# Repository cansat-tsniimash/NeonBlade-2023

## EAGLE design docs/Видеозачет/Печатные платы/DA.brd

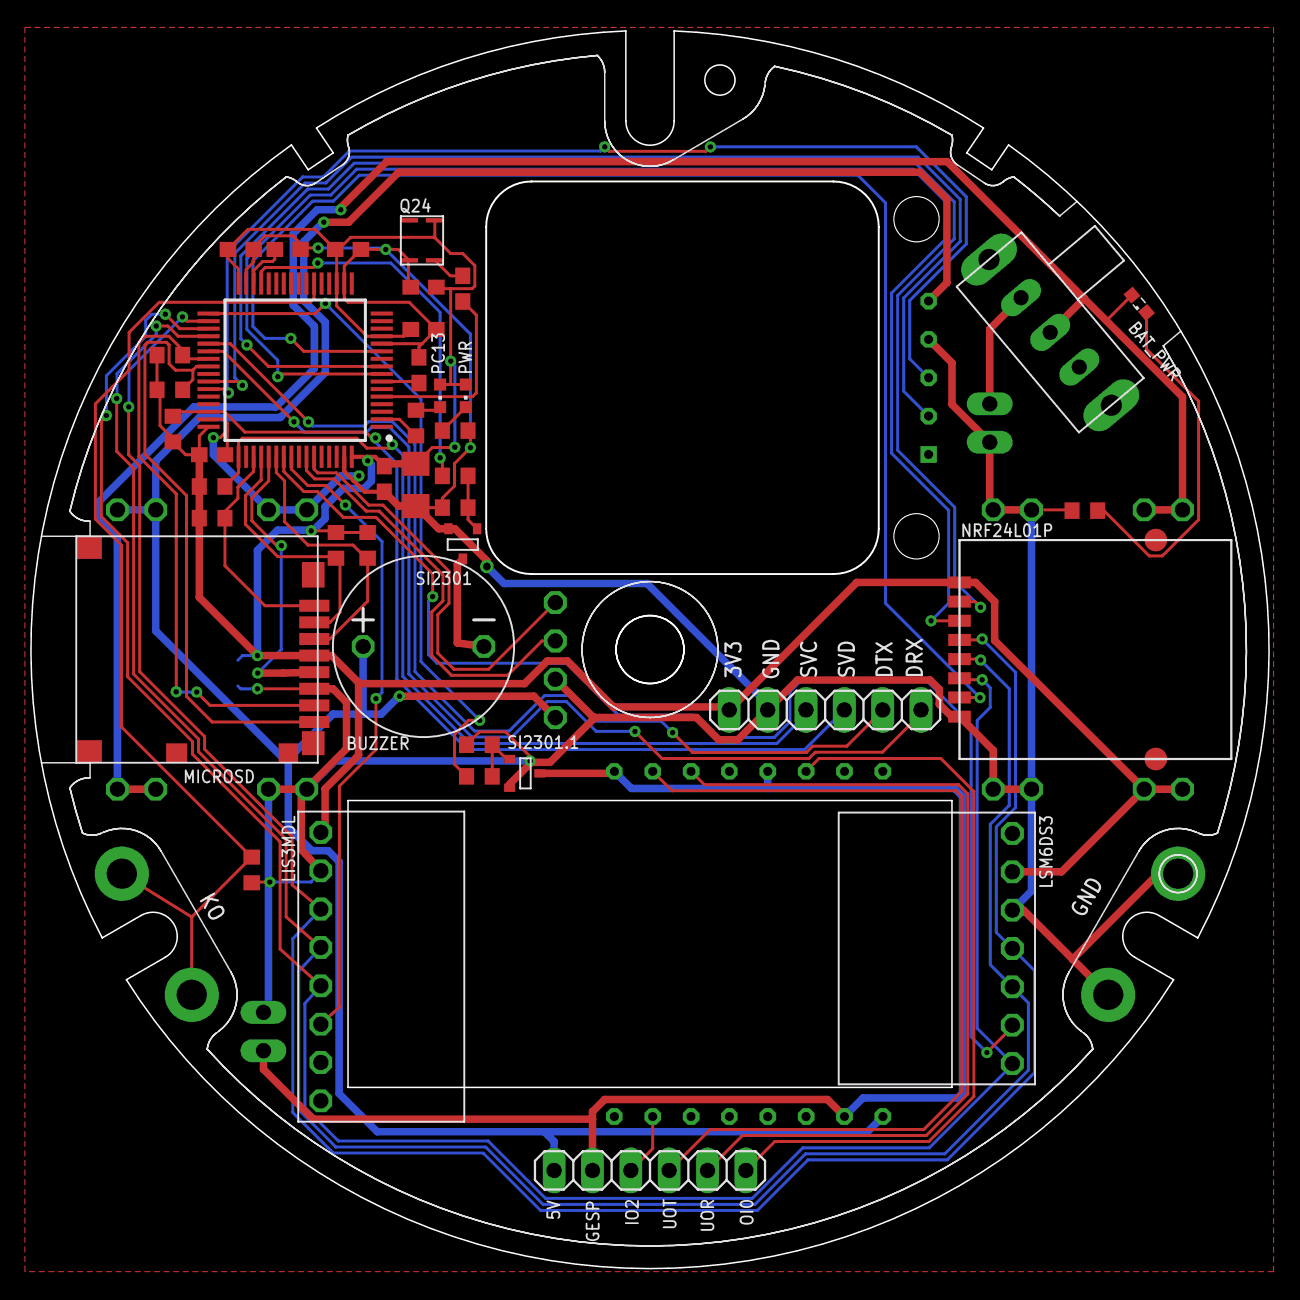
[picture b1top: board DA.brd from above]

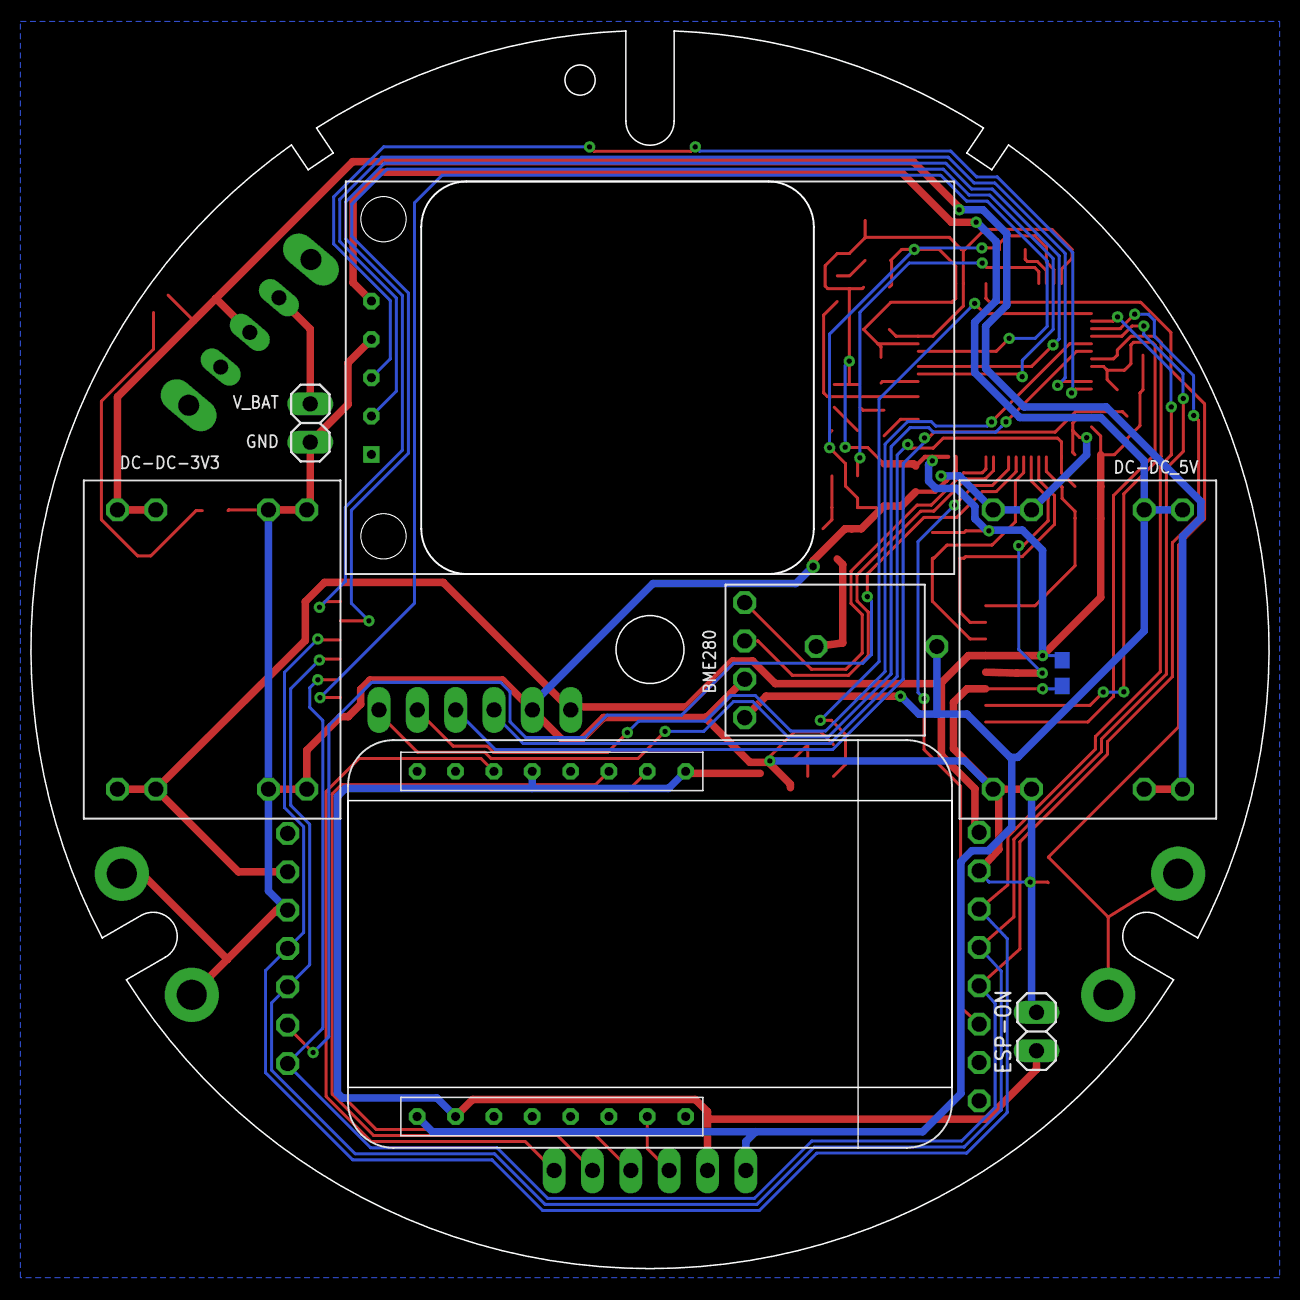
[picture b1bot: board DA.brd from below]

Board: 2 copper layers, 82.0 x 82.0 mm, 48 parts (7 on the bottom side), 46 nets.

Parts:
BAT_PWR: SML0603
BME280: BME280BME280-PINS-ONLY; BME280-PINS-ONLY
BUZZER: BUZZERS8R6; BUZZER-S8R12
C1, C3, C4, C5, C6, C7: 100nF; C0603
C2: 10uF; C1206
C8: 1nF; C0603
C9: 100nf; C0603
C10: 10nF; C0603
C11: 4.7uf; C0603
DC-DC-3V3: MP1584-B
DC-DC_5V: MP1584-B
ESP32-CAM: ESP32-CAM
ESP-ON: 1X02
JP1, JP3: 1X06
JP2: 1X02
LIS3MDL: LIS3MDL-CJMCUбез_отв.; LIS3MDL-CGMSU-NB2023-1
LSM6DS3: LSM6DS3-GY-NB2023Без_отв.; LSM6DS3-GY-NB2023-1
MICROSD: SD
NRF24L01P: NRF24L01_ML01SP4
PC13: CHIPLED_0603
PWR: CHIPLED_0603
Q24: Q24
R1: 5K1; R0603
R2, R7, R8, R9, R10: 3k3; R0603
R3, R4: 2k; R0603
R5, R6, R31, R32, R33: 10k; R0603
R30, R34: 100R; R0603
S1: SWITCH_SK-12F14
SI2301, SI2301.1: MOSFET-N; SOT23-3
STM32F0401: STM32F401RCT6; QFP50P1200X1200X160-64N
U$5: GPS_NEO7M_W-PPS; GPS_NEO7M_W-PPS_&_ANT

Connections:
3V3: C1.2, C2.1, C3.2, C4.1, C5.1, C6.1, C7.2, C10.2, DC-DC-3V3.P$7, DC-DC-3V3.P$8, JP1.6, LIS3MDL.P$1, LSM6DS3.P$6, MICROSD.VDD, NRF24L01P.P$1, PC13.A, PWR.A, Q24.P$4, R2.2, R5.2, R6.2, R7.2, R8.2, R9.2, R10.2, STM32F0401.13, STM32F0401.19, STM32F0401.32, STM32F0401.48, STM32F0401.64
5V: BME280.P$1, BUZZER.P$1, DC-DC_5V.P$7, DC-DC_5V.P$8, ESP32-CAM.P$1, JP3.1, U$5.VCC
BASS_BUZZER: R30.1, STM32F0401.29
CE_NRF: NRF24L01P.P$2, STM32F0401.9
CS_LIS: LIS3MDL.P$6, STM32F0401.56
CS_LSM: LSM6DS3.P$2, STM32F0401.55
CS_NRF: NRF24L01P.P$3, STM32F0401.8
DBG_RX: JP1.1, STM32F0401.38
DBG_TX: JP1.2, STM32F0401.37
ESP_EN: R34.1, STM32F0401.33
GND: BME280.P$2, C1.1, C2.2, C3.1, C4.2, C5.2, C6.2, C7.1, C9.1, C10.1, C11.2, DC-DC-3V3.P$3, DC-DC-3V3.P$4, DC-DC-3V3.P$5, DC-DC-3V3.P$6, DC-DC_5V.P$3, DC-DC_5V.P$4, DC-DC_5V.P$5, DC-DC_5V.P$6, ESP-ON.1, JP1.5, JP2.2, LIS3MDL.P$2, LSM6DS3.P$5, MICROSD.VSS, NRF24L01P.P$8, Q24.P$2, R1.2, R3.1, R31.2, R32.1, R33.1, SI2301.2, SI2301.1.2, STM32F0401.12, STM32F0401.18, STM32F0401.31, STM32F0401.47, STM32F0401.63, U$5.GND
GND_ESP: ESP32-CAM.P$2, ESP32-CAM.P$12, ESP32-CAM.P$16, ESP-ON.2, JP3.2, SI2301.1.3
GPS_RX: STM32F0401.43, U$5.TX
GPS_TX: STM32F0401.42, U$5.RX
IO0: ESP32-CAM.P$11, JP3.6
IO2: ESP32-CAM.P$7, JP3.3
KO: R32.2, STM32F0401.22
LED: R4.1, STM32F0401.2
MISO: LIS3MDL.P$5, LSM6DS3.P$1, NRF24L01P.P$6, STM32F0401.35
MOSI: LIS3MDL.P$4, LSM6DS3.P$3, NRF24L01P.P$5, STM32F0401.36
unnamed: R30.2, R31.1, SI2301.1
unnamed: R33.2, R34.2, SI2301.1.1
unnamed: BAT_PWR.C, R1.1
unnamed: JP2.1, S1.P$5
unnamed: C8.2, Q24.P$3
unnamed: C11.1, STM32F0401.30
unnamed: BUZZER.P$2, SI2301.3
unnamed: PWR.C, R3.2
unnamed: PC13.C, R4.2
NRF_IRQ: NRF24L01P.P$7, STM32F0401.11
NRST: C9.2, STM32F0401.7
SCK: LIS3MDL.P$3, LSM6DS3.P$4, NRF24L01P.P$4, STM32F0401.34
SCL: BME280.P$3, STM32F0401.58
SDA: BME280.P$4, STM32F0401.59
SDIO_CK: MICROSD.CLK, STM32F0401.53
SDIO_CMD: MICROSD.CMD, R8.1, STM32F0401.54
SDIO_DAT0: MICROSD.DAT0, R9.1, STM32F0401.39
SDIO_DAT1: MICROSD.DAT1, R10.1, STM32F0401.40
SDIO_DAT2: MICROSD.DAT2, R2.1, STM32F0401.51
SDIO_DAT3: MICROSD.DAT3, R7.1, STM32F0401.52
SVC: JP1.4, R6.1, STM32F0401.49
SVD: JP1.3, R5.1, STM32F0401.46
TCXO: C8.1, STM32F0401.5
UOR: ESP32-CAM.P$14, JP3.5
UOT: ESP32-CAM.P$15, JP3.4
V_BAT: BAT_PWR.A, DC-DC-3V3.P$1, DC-DC-3V3.P$2, DC-DC_5V.P$1, DC-DC_5V.P$2, S1.P$3

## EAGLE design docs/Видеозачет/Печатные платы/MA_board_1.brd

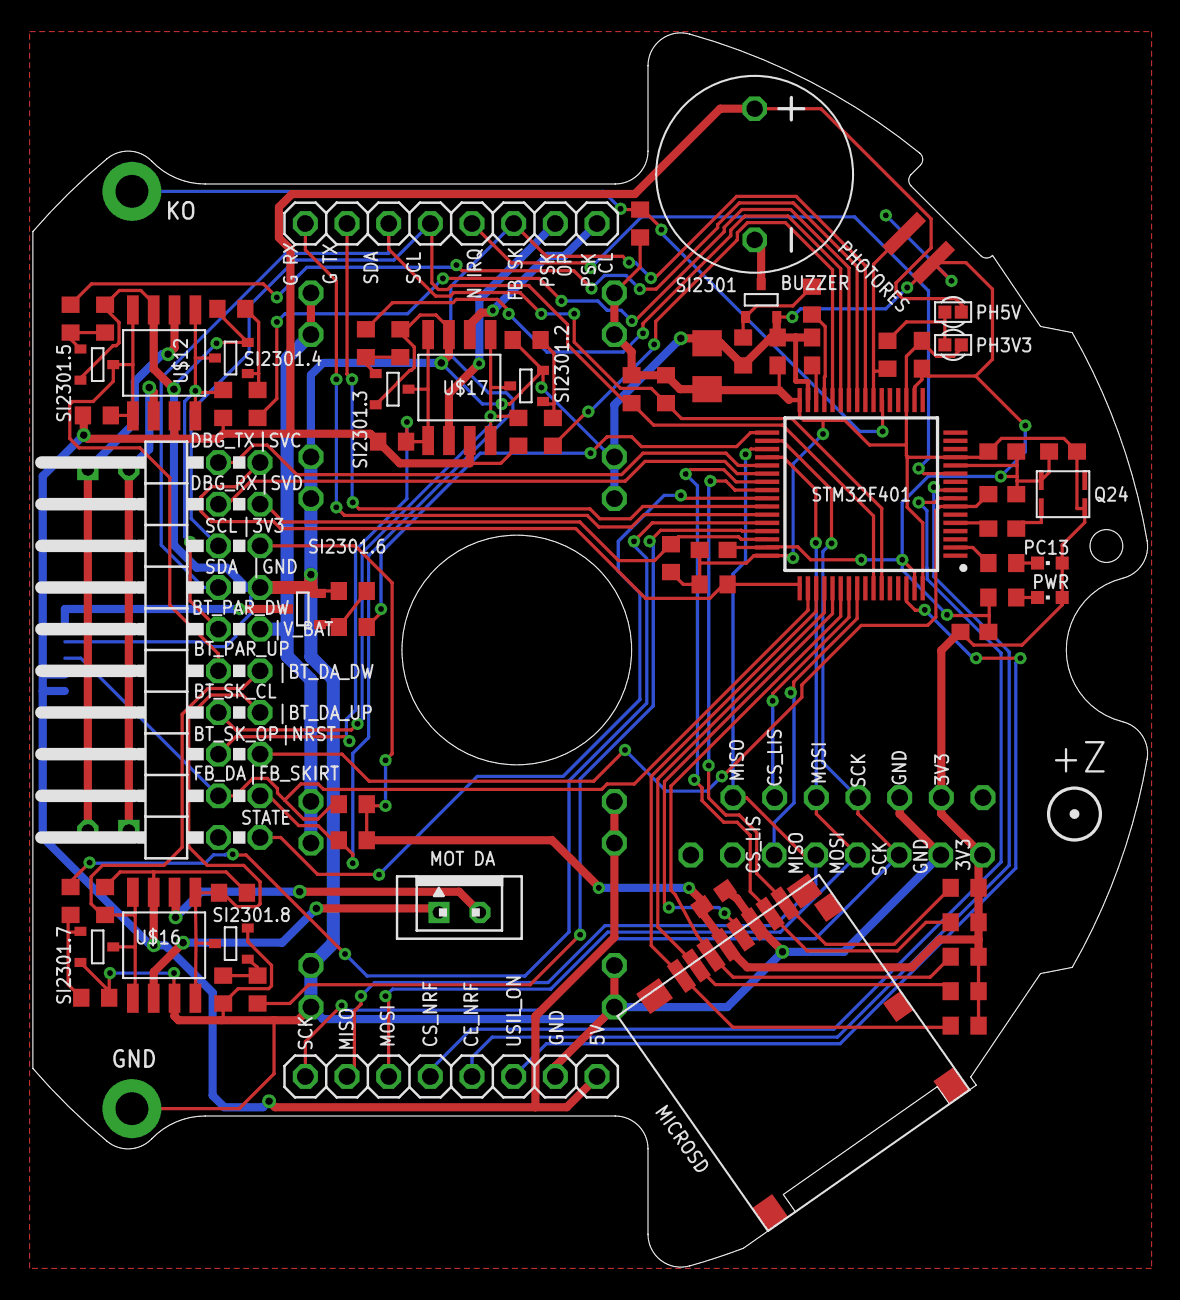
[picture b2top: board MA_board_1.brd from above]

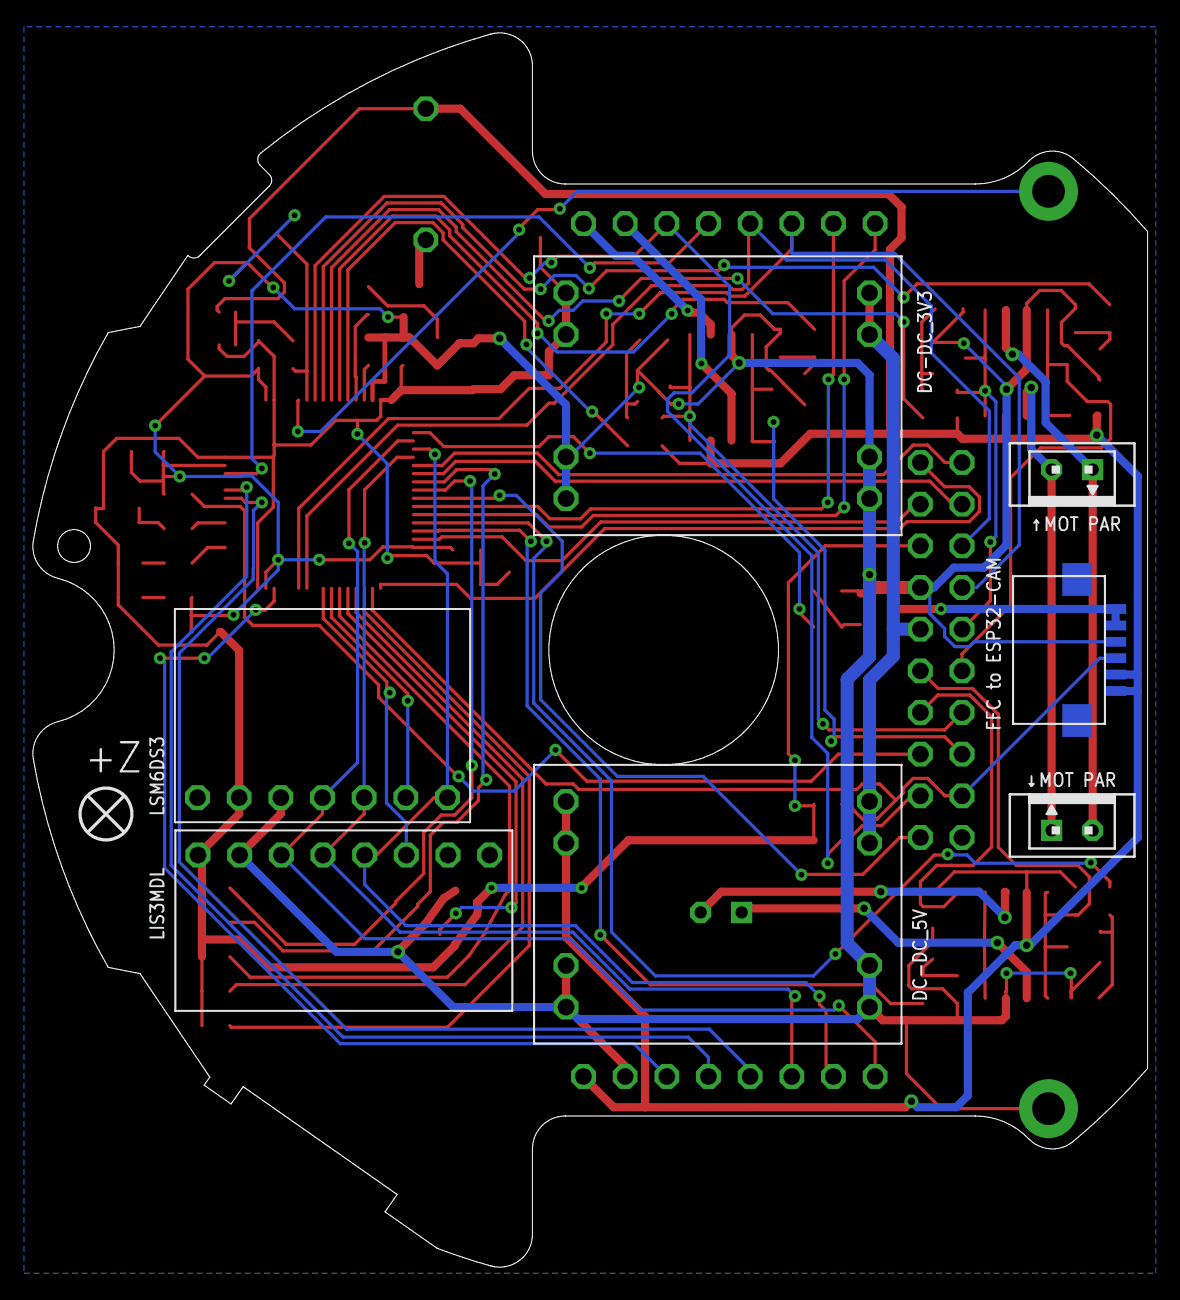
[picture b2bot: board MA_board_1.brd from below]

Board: 2 copper layers, 68.0 x 75.2 mm, 79 parts (5 on the bottom side), 70 nets.

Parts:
3V3, 5V: VIAS-CONNECT
BUZZER: BUZZERS8R6; BUZZER-S8R12
C1, C3, C4, C5, C6, C7, C9: 100nF; C0603
C2: 10uF; C1206
C8: 1nF; C0603
C10: 10nF; C0603
C11: 4.7uf; C0603
DC-DC_3V3, DC-DC_5V: MP1584-B
JP1: 2X10/90
JP2, JP3, JP4: JST-2-K-S; B2B-PH-K-S
JP6, JP7: 1X08
LIS3MDL: LIS3MDL-CJMCUБез_отв._зеркальный; LIS3MDL-CGMSU-NB2023
LSM6DS3: LSM6DS3-GY-NB2023
MICROSD: SD
PC13: CHIPLED_0603
PHOTORES: PHOTORES_VT93N1; PHOTORES_VT93N1_SMD
PWR: CHIPLED_0603
Q24: Q24
R1, R5, R6, R11, R12, R13, R14, R18, R19, R20, R21, R24, R25, R26, R27, R31, R33, R35: 10k; R0603
R2, R7, R8, R9, R10: 3k3; R0603
R3, R4: 2k; R0603
R15, R16, R22, R23, R28, R29, R30, R34: 100R; R0603
R17: 191k/2k; R0603
R32: 3k9; R0603
R36, R37: 4k7; R0603
SI2301, SI2301.2, SI2301.3, SI2301.4, SI2301.5, SI2301.6, SI2301.7, SI2301.8: MOSFET-N; SOT23-3
STM32F401: STM32F401RCT6; QFP50P1200X1200X160-64N
U$8: FCC-CONNECT-6P; FFC-CONNECT-6P-SMD
U$12, U$16, U$17: MOSFET_2P+2N_AP9930GM; SO8

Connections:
3V3: 3V3.1, C1.2, C2.1, C3.2, C4.1, C5.1, C6.1, C7.2, C10.2, DC-DC_3V3.P$7, DC-DC_3V3.P$8, JP1.15, LIS3MDL.P$1, LSM6DS3.P$6, MICROSD.VDD, PC13.A, PWR.A, Q24.P$4, R1.2, R2.2, R5.2, R6.2, R7.2, R8.2, R9.2, R10.2, R32.1, R35.1, R36.2, R37.2, STM32F401.13, STM32F401.19, STM32F401.32, STM32F401.48, STM32F401.64
5V: 5V.2, BUZZER.P$1, DC-DC_5V.P$7, DC-DC_5V.P$8, JP6.8, R12.2, R13.2, R19.2, R20.2, R25.2, R26.2, U$8.P$5, U$8.P$6, U$12.7, U$16.7, U$17.7
BASS_BUZZER: R30.1, STM32F401.29
BOTTON_DA_DOWN: JP1.9, R13.1, SI2301.7.3, U$16.1, U$16.8
BOTTON_DA_UP: JP1.7, R12.1, SI2301.8.3, U$16.4, U$16.5
BOTTON_PAR_DOWN: JP1.12, R20.1, SI2301.4.3, U$12.1, U$12.8
BOTTON_PAR_UP: JP1.10, R19.1, SI2301.5.3, U$12.4, U$12.5
BOTTON_SKIRT_CLOSE: JP1.8, R26.1, SI2301.2.3, U$17.1, U$17.8
BOTTON_SKIRT_OPEN: JP1.6, R25.1, SI2301.3.3, U$17.4, U$17.5
CE_NRF: JP6.5, STM32F401.9
CS_LIS: LIS3MDL.P$6, STM32F401.56
CS_LSM: LSM6DS3.P$2, STM32F401.55
CS_NRF: JP6.4, STM32F401.8
DBG_RX: JP1.18, STM32F401.38
DBG_TX: JP1.20, STM32F401.37
ESP_EN: R34.1, STM32F401.33
FEEDBACK_DA: JP1.4, R35.2, STM32F401.50, U$8.P$4
FEEDBACK_SKIRT: JP1.3, JP7.6, R1.1, STM32F401.24
GND: C1.1, C2.2, C3.1, C4.2, C5.2, C6.2, C7.1, C9.1, C10.1, C11.2, DC-DC_3V3.P$3, DC-DC_3V3.P$4, DC-DC_3V3.P$5, DC-DC_3V3.P$6, DC-DC_5V.P$3, DC-DC_5V.P$4, DC-DC_5V.P$5, DC-DC_5V.P$6, JP1.13, JP6.7, LIS3MDL.P$2, LSM6DS3.P$5, MICROSD.VSS, PHOTORES.P$1, Q24.P$2, R3.1, R11.1, R14.1, R18.1, R21.1, R24.1, R27.1, R31.2, R33.1, SI2301.2, SI2301.2.2, SI2301.3.2, SI2301.4.2, SI2301.5.2, SI2301.6.2, SI2301.7.2, SI2301.8.2, STM32F401.12, STM32F401.18, STM32F401.31, STM32F401.47, STM32F401.63, U$8.P$3, U$12.3, U$16.3, U$17.3
GND_ESP: SI2301.6.3, U$8.P$1, U$8.P$2
GPS_RX: JP7.1, STM32F401.43
GPS_TX: JP7.2, STM32F401.42
KO: R32.2, STM32F401.22
LED: R4.1, STM32F401.2
MISO: JP6.2, LIS3MDL.P$5, LSM6DS3.P$1, STM32F401.35
MOSI: JP6.3, LIS3MDL.P$4, LSM6DS3.P$3, STM32F401.36
MOTOR_DA_DOWN: R15.1, STM32F401.44
MOTOR_DA_UP: R16.2, STM32F401.45
MOTOR_PAR_DOWN: R22.1, STM32F401.26
MOTOR_PAR_UP: R23.2, STM32F401.25
MOTOR_SKIRT_CLOSE: R28.1, STM32F401.28
MOTOR_SKIRT_OPEN: R29.2, STM32F401.27
unnamed: R30.2, R31.1, SI2301.1
unnamed: R11.2, R15.2, SI2301.7.1
unnamed: R18.2, R22.2, SI2301.4.1
unnamed: R33.2, R34.2, SI2301.6.1
unnamed: JP3.1, JP4.2, U$12.2
unnamed: JP2.1, U$16.2
unnamed: JP2.2, U$16.6
unnamed: R14.2, R16.1, SI2301.8.1
unnamed: JP3.2, JP4.1, U$12.6
unnamed: C8.2, Q24.P$3
unnamed: R21.2, R23.1, SI2301.5.1
unnamed: C11.1, STM32F401.30
unnamed: 3V3.2, 5V.1, R17.1
unnamed: R24.2, R28.2, SI2301.2.1
unnamed: R27.2, R29.1, SI2301.3.1
unnamed: BUZZER.P$2, SI2301.3
unnamed: PWR.C, R3.2
unnamed: PC13.C, R4.2
NRF_IRQ: JP7.5, STM32F401.11
NRST: C9.2, JP1.5, STM32F401.7
PHOTORES: PHOTORES.P$2, R17.2, STM32F401.23
POWER_SKIRT_CLOSE: JP7.8, U$17.2
POWER_SKIRT_OPEN: JP7.7, U$17.6
SCK: JP6.1, LIS3MDL.P$3, LSM6DS3.P$4, STM32F401.34
SCL: JP1.16, JP7.4, R37.1, STM32F401.58
SDA: JP1.14, JP7.3, R36.1, STM32F401.59
SDIO_CK: MICROSD.CLK, STM32F401.53
SDIO_CMD: MICROSD.CMD, R8.1, STM32F401.54
SDIO_DAT0: MICROSD.DAT0, R9.1, STM32F401.39
SDIO_DAT1: MICROSD.DAT1, R10.1, STM32F401.40
SDIO_DAT2: MICROSD.DAT2, R2.1, STM32F401.51
SDIO_DAT3: MICROSD.DAT3, R7.1, STM32F401.52
STATE: JP1.1, STM32F401.41
SVC: JP1.19, R6.1, STM32F401.49
SVD: JP1.17, R5.1, STM32F401.46
TCXO: C8.1, STM32F401.5
USIL_ON: JP6.6, STM32F401.62
V_BAT: DC-DC_3V3.P$1, DC-DC_3V3.P$2, DC-DC_5V.P$1, DC-DC_5V.P$2, JP1.11

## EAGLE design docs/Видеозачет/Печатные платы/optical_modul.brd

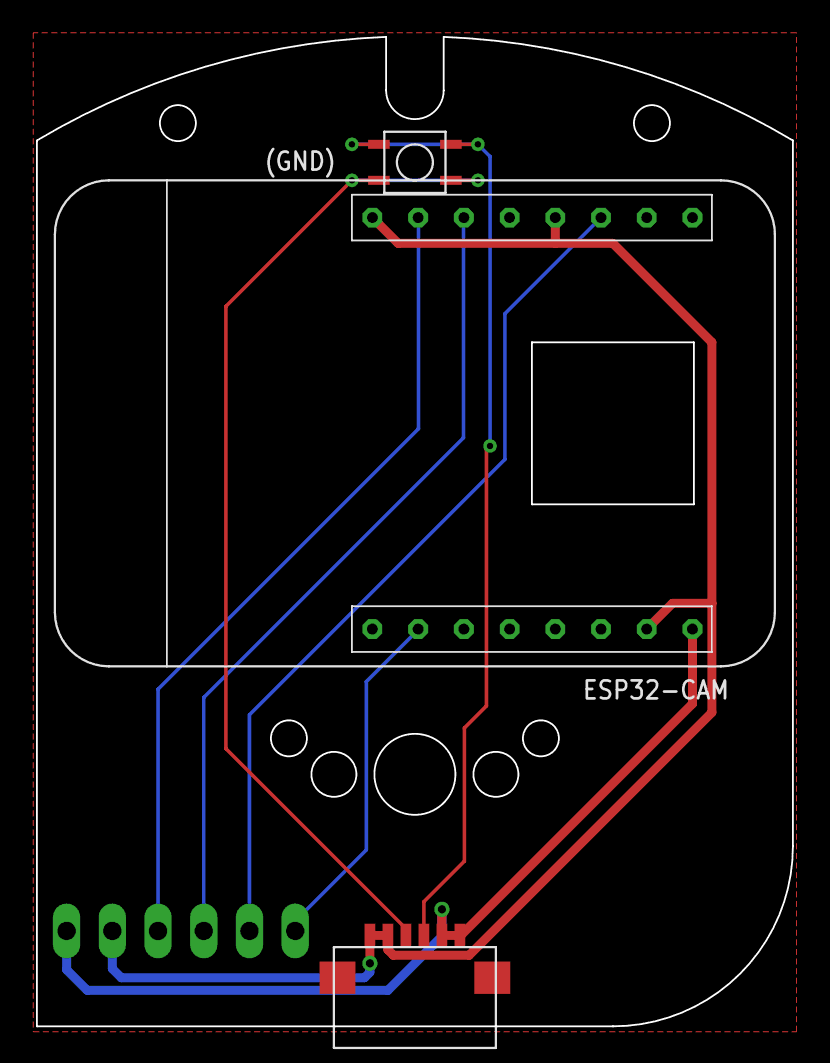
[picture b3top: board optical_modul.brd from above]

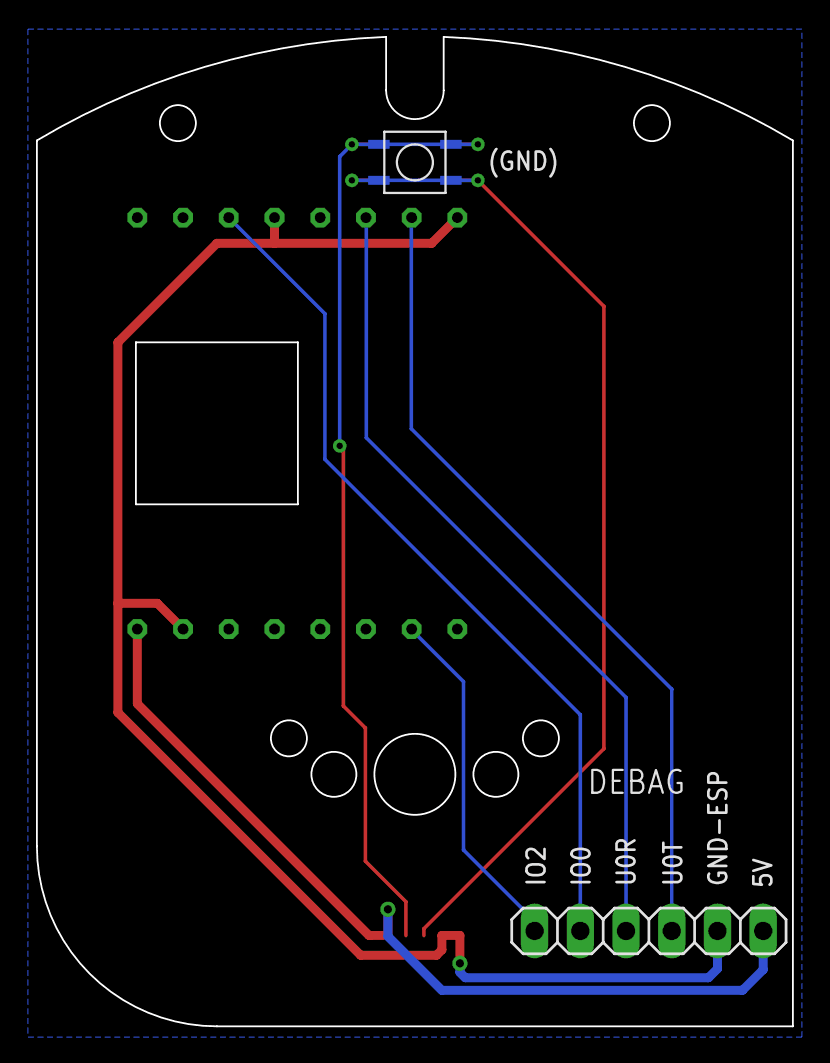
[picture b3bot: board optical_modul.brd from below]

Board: 2 copper layers, 42.0 x 55.0 mm, 5 parts (2 on the bottom side), 8 nets.

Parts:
DEBAG: 1X06
ESP32-CAM: ESP32-CAM
U$1: FCC-CONNECT-6P; FFC-CONNECT-6P-SMD
U$2, U$3: BTN_VERY_SMALL

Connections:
5V: DEBAG.1, ESP32-CAM.P$1, U$1.P$5, U$1.P$6
FEEDBACK_DA: U$1.P$4, U$2.P$1, U$2.P$2, U$3.P$1, U$3.P$2
GND: U$1.P$3, U$2.P$3, U$2.P$4, U$3.P$3, U$3.P$4
GND_ESP: DEBAG.2, ESP32-CAM.P$2, ESP32-CAM.P$12, ESP32-CAM.P$16, U$1.P$1, U$1.P$2
IO0: DEBAG.5, ESP32-CAM.P$11
IO2: DEBAG.6, ESP32-CAM.P$7
U0R: DEBAG.4, ESP32-CAM.P$14
U0T: DEBAG.3, ESP32-CAM.P$15
